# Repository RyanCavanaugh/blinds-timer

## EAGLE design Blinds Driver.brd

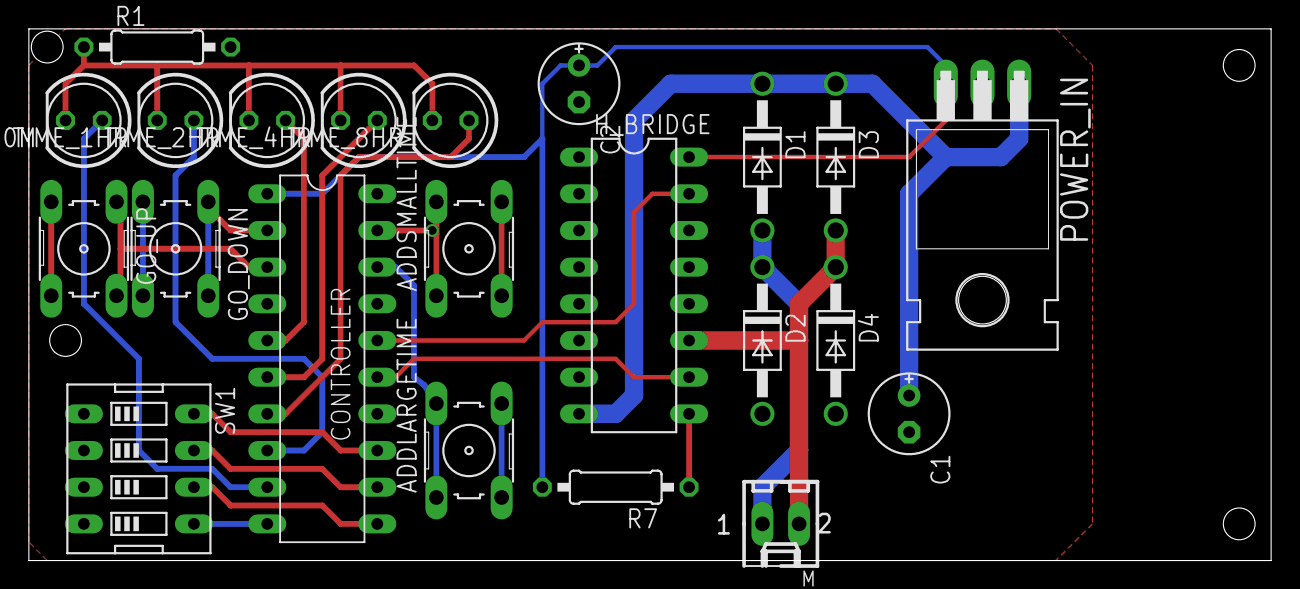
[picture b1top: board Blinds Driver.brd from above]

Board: 2 copper layers, 86.0 x 36.8 mm, 22 parts (0 on the bottom side), 22 nets.

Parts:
ADDLARGETIME: B3F-10XX
ADDSMALLTIME: B3F-10XX
C1, C2: 1u; E2,5-6E
CONTROLLER: DIL20
D1, D2, D3, D4: 1N4004; DO41-10
GO_DOWN: B3F-10XX
GO_UP: B3F-10XX
H_BRIDGE: L293D; DIL16
M: 22-27-2021-02; 6410-02
POWER_IN: 7805T; TO220H
R1, R7: 0207/10
SW1: EDG-04
TIME_1HR, TIME_2HR, TIME_4HR, TIME_8HR, TIME_30M: LED5MM

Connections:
+5V: C2.+, CONTROLLER.1, H_BRIDGE.16, POWER_IN.3, R7.2
+12V: C1.+, D1.C, D3.C, H_BRIDGE.8, POWER_IN.1
GND: ADDLARGETIME.3, ADDLARGETIME.4, ADDSMALLTIME.3, ADDSMALLTIME.4, C1.-, C2.-, CONTROLLER.4, CONTROLLER.14, CONTROLLER.17, CONTROLLER.20, D2.A, D4.A, GO_DOWN.3, GO_DOWN.4, GO_UP.3, GO_UP.4, H_BRIDGE.1, H_BRIDGE.2, H_BRIDGE.4, H_BRIDGE.5, H_BRIDGE.7, H_BRIDGE.12, H_BRIDGE.13, POWER_IN.2, R1.2, SW1.1, SW1.2, SW1.3, SW1.4
M1CONTROL: CONTROLLER.16, H_BRIDGE.15
M2CONTROL: CONTROLLER.15, H_BRIDGE.10
unnamed: CONTROLLER.10, SW1.5
unnamed: D1.A, D2.C, H_BRIDGE.14, M.1
unnamed: CONTROLLER.11, SW1.6
unnamed: CONTROLLER.12, SW1.7
unnamed: D3.A, D4.C, H_BRIDGE.11, M.2
unnamed: CONTROLLER.13, SW1.8
unnamed: H_BRIDGE.9, R7.1
unnamed: CONTROLLER.7, TIME_8HR.A
unnamed: CONTROLLER.6, TIME_4HR.A
unnamed: CONTROLLER.5, TIME_2HR.A
unnamed: CONTROLLER.8, TIME_1HR.A
unnamed: R1.1, TIME_1HR.K, TIME_2HR.K, TIME_4HR.K, TIME_8HR.K, TIME_30M.K
unnamed: ADDSMALLTIME.1, ADDSMALLTIME.2, CONTROLLER.19
unnamed: ADDLARGETIME.1, ADDLARGETIME.2, CONTROLLER.18
unnamed: CONTROLLER.3, GO_UP.1, GO_UP.2
unnamed: CONTROLLER.2, GO_DOWN.1, GO_DOWN.2
unnamed: CONTROLLER.9, TIME_30M.A

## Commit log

2015-05-26 Add brd + sch
2015-05-26 Shrinkage!
2015-05-26 Miniaturize and remove last via
2015-05-26 Slightly smaller, changes holes, improve solderability
2015-05-26 Soldering tweak
2015-05-26 Standardize trace widths
2015-05-26 Fit into smaller PCB! Use 4-pin DIP
2015-05-26 Improve clearances
2015-05-26 More tweaks
2015-05-29 1) Diodes were doubled up 2) Only one half-bridge is needed 3) VCC 2 is +12V, VCC1 is +5V 4) Added 2 bypass capacitors on the power supply lines to stabilize power supply
2015-06-07 Pin A3 is input-only, so use C7 instead
2015-06-07 Add documentation
2015-06-07 Organize into folders, add firmware files
